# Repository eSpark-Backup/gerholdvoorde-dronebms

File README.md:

# Gerhold Voorde - Drone BMS Circuit Design

## Project Requirements
[Requirements Document](https://docs.google.com/document/d/1HwCwU0NZK4SfBbceRvGtYb6am0WZ7dugDeT3MsA2zgc/edit?usp=sharing)  
[Datasheet](https://www.analog.com/media/en/technical-documentation/data-sheets/MAX17201-MAX17215.pdf)  
[PCB Design Document](https://www.analog.com/media/en/technical-documentation/user-guides/max1720xmax1721x-system-side-implementation-guide.pdf)

### Important Points
* PCB should be designed considering maximum of 20A of discharge current from the battery.
* See possiblity and create overlay for battery so that it makes it convenient for placement in future.

### Reference component URLs
1. https://nl.farnell.com/multicomp/mcwr06x1500ftl/res-150r-1-0-1w-0603-thick-film/dp/2446572
2. https://nl.farnell.com/tdk/c1608x7r1v474k080ae/cap-0-47uf-35v-mlcc-0603/dp/3489827
3. https://nl.farnell.com/multicomp-pro/mcsr06x103-jtl/res-10k-5-0-1w-0603-thick-film/dp/2074170
4. https://nl.farnell.com/multicomp/mc0603b104j160ct/cap-0-1-f-16v-5-x7r-0603-reel/dp/2310627

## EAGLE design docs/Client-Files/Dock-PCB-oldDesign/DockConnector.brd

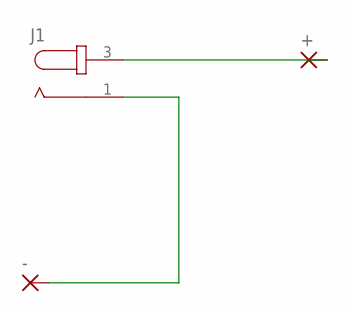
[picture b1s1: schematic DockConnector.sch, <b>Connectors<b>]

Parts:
+: WIREPAD_2,54/1,1
-: WIREPAD_2,54/1,1
J1: CON-JACK_JACK-PLUG0; CON-JACK_SPC4077

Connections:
unnamed: +.1, J1.3
unnamed: -.1, J1.1

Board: 2 copper layers, 3 parts (0 on the bottom side), 2 nets, no tracks yet.

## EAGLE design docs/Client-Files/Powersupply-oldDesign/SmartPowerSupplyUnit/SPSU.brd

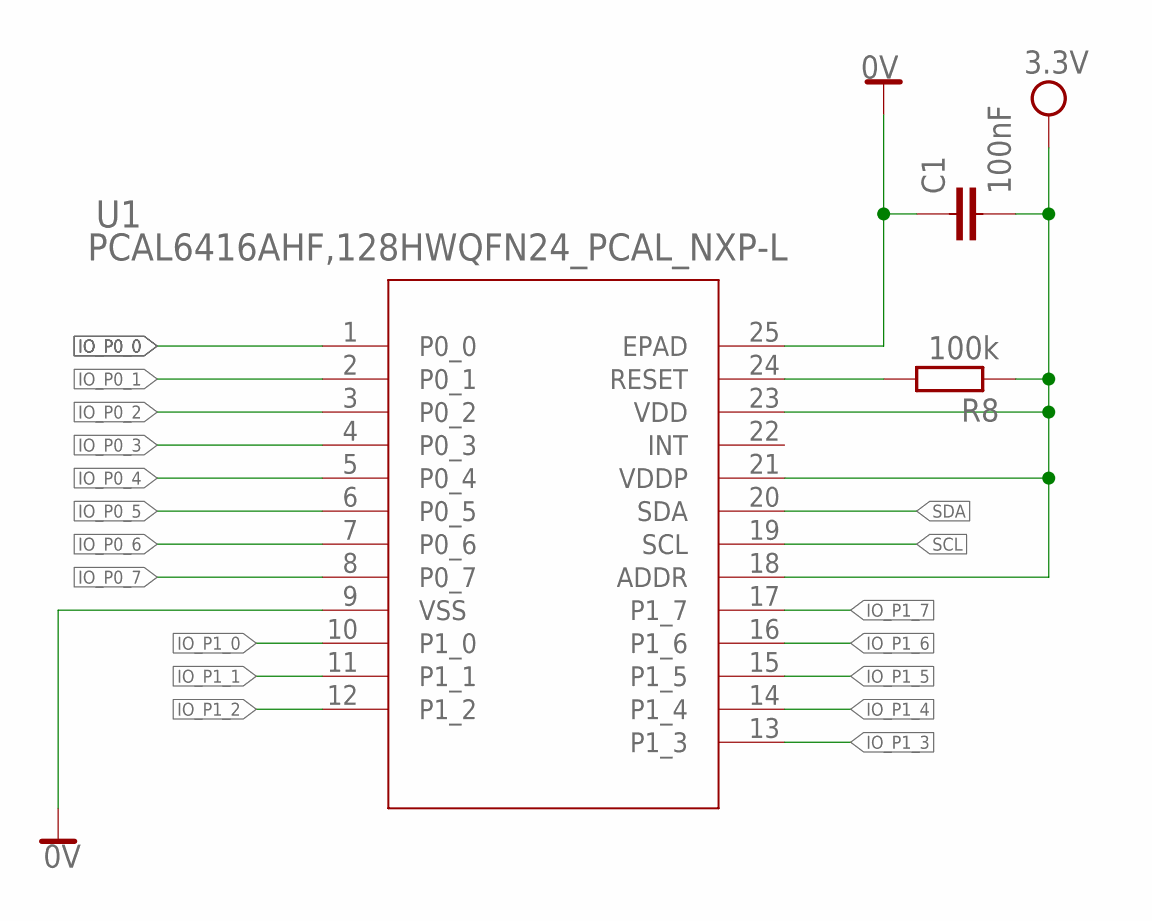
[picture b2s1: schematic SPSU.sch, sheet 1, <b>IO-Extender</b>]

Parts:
C1: 100nF; C0603
R8: 100k; R0603; FARNELL 2447226
U1: PCAL6416AHF,128HWQFN24_PCAL_NXP-L; HWQFN24_PCAL_NXP-L

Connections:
0V: C1.1, U1.9 (VSS), U1.25 (EPAD); also elsewhere on the board
IO_P0_0: U1.1 (P0_0); also elsewhere on the board
IO_P0_1: U1.2 (P0_1); also elsewhere on the board
IO_P0_2: U1.3 (P0_2); also elsewhere on the board
IO_P0_3: U1.4 (P0_3); also elsewhere on the board
IO_P0_4: U1.5 (P0_4); also elsewhere on the board
IO_P0_5: U1.6 (P0_5); also elsewhere on the board
IO_P0_6: U1.7 (P0_6); also elsewhere on the board
IO_P0_7: U1.8 (P0_7)
IO_P1_0: U1.10 (P1_0)
IO_P1_1: U1.11 (P1_1)
IO_P1_2: U1.12 (P1_2); also elsewhere on the board
IO_P1_3: U1.13 (P1_3)
IO_P1_4: U1.14 (P1_4)
IO_P1_5: U1.15 (P1_5)
IO_P1_6: U1.16 (P1_6)
IO_P1_7: U1.17 (P1_7)
unnamed: R8.2, U1.24 (RESET)
SCL: U1.19 (SCL); also elsewhere on the board
SDA: U1.20 (SDA); also elsewhere on the board
VDD: C1.2, R8.1, U1.18 (ADDR), U1.21 (VDDP), U1.23 (VDD); also elsewhere on the board

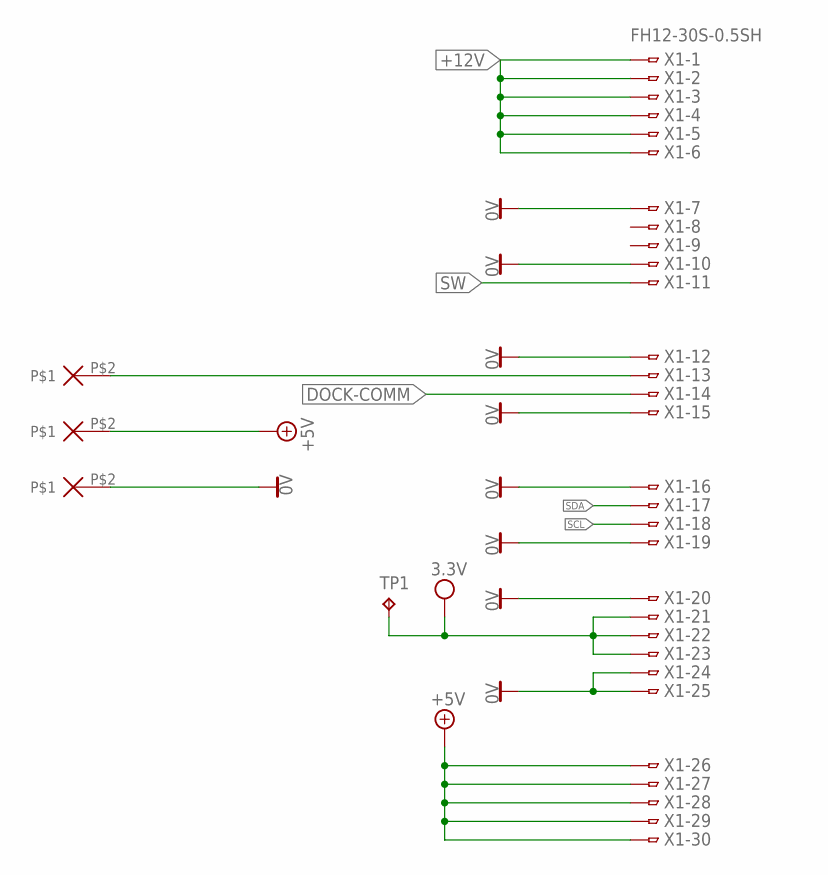
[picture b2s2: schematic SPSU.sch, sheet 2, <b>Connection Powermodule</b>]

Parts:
+: TH-0.75/0.6
-: TH-0.75/0.6
D: TH-0.75/0.6
TP1: TPTP11R; TP11R
X1: FH12-30S-0.5SH

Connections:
0V: -.P$2, X1.7, X1.10, X1.12, X1.15, X1.16, X1.19, X1.20, X1.24, X1.25; also elsewhere on the board
+5V: +.P$2, X1.26, X1.27, X1.28, X1.29, X1.30; also elsewhere on the board
+12V: X1.1, X1.2, X1.3, X1.4, X1.5, X1.6; also elsewhere on the board
DOCK-COMM: X1.14; also elsewhere on the board
unnamed: D.P$2, X1.13
SCL: X1.18; also elsewhere on the board
SDA: X1.17; also elsewhere on the board
SW: X1.11; also elsewhere on the board
VDD: TP1.TP, X1.21, X1.22, X1.23; also elsewhere on the board

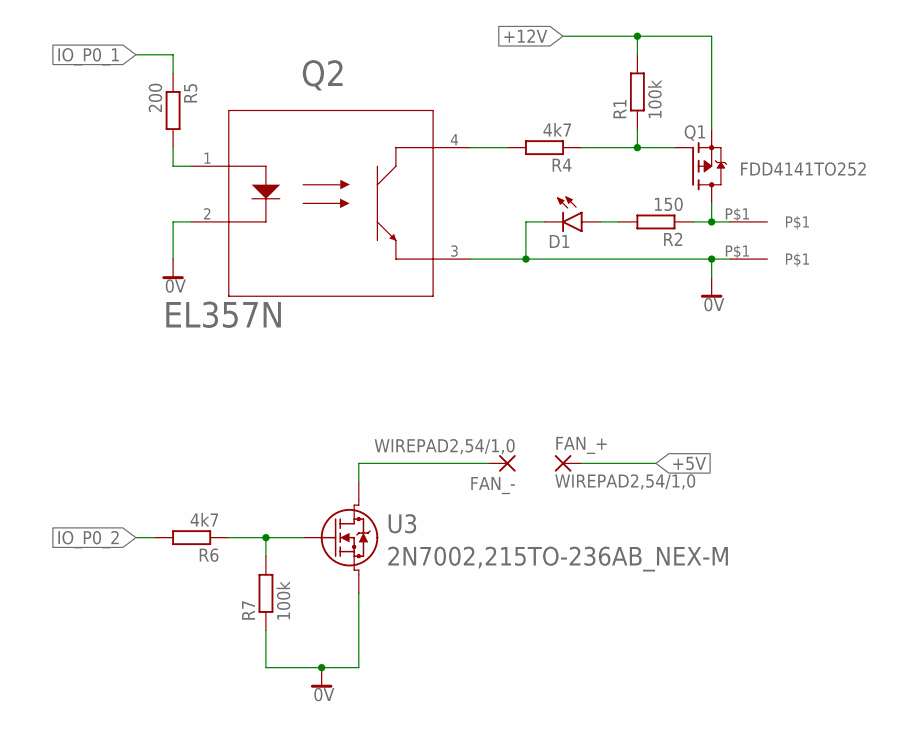
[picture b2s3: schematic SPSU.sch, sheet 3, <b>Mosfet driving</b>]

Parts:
D1: LEDCHIPLED_0805; CHIPLED_0805
ESC+: ESC
ESC-: ESC
FAN_+: WIREPAD2,54/1,0; 2,54/1,0
FAN_-: WIREPAD2,54/1,0; 2,54/1,0
Q1: FDD4141TO252; TO252
Q2: EL357N; EL357N(C)(TA)-VG_EVE-L
R1, R7: 100k; R0603
R2: 150; R0603
R4, R6: 4k7; R0603
R5: 200; R0603
U3: 2N7002,215TO-236AB_NEX-M; TO-236AB_NEX-M

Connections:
0V: D1.C, ESC-.P$1, Q2.2, Q2.3, R7.1, U3.2 (3); also elsewhere on the board
+5V: FAN_+.1; also elsewhere on the board
+12V: Q1.2 (S), R1.2; also elsewhere on the board
ESC_+: ESC+.P$1, Q1.3 (D), R2.1
IO_P0_1: R5.1; also elsewhere on the board
IO_P0_2: R6.2; also elsewhere on the board
unnamed: Q1.1 (G), R1.1, R4.1
unnamed: D1.A, R2.2
unnamed: Q2.4, R4.2
unnamed: Q2.1, R5.2
unnamed: R6.1, R7.2, U3.1
unnamed: FAN_-.1, U3.3 (2)

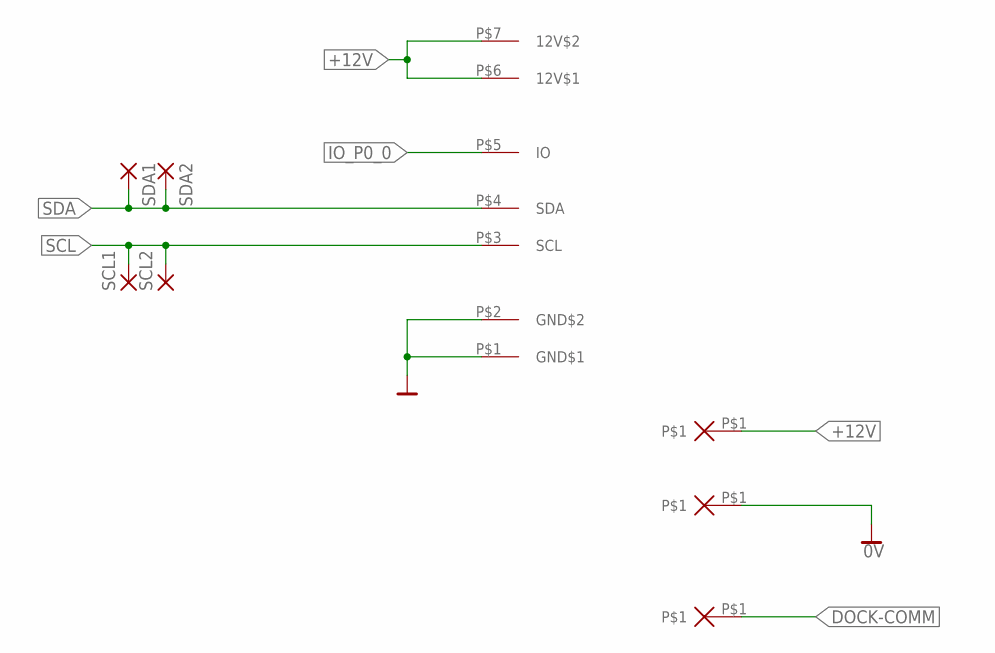
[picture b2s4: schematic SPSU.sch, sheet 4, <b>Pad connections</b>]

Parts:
CHG+: SMT-PAD_SQ6MM
CHG-: SMT-PAD_SQ6MM
SCL1, SCL2: 1,6/0,8
SDA1, SDA2: 1,6/0,8
U$1: BATT_CON_THT
U$2: SMT-PAD_R3MM

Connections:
0V: CHG-.P$1, U$1.P$1 (GND$1), U$1.P$2 (GND$2); also elsewhere on the board
+12V: CHG+.P$1, U$1.P$6 (12V$1), U$1.P$7 (12V$2); also elsewhere on the board
DOCK-COMM: U$2.P$1; also elsewhere on the board
IO_P0_0: U$1.P$5 (IO); also elsewhere on the board
SCL: SCL1.1, SCL2.1, U$1.P$3 (SCL); also elsewhere on the board
SDA: SDA1.1, SDA2.1, U$1.P$4 (SDA); also elsewhere on the board

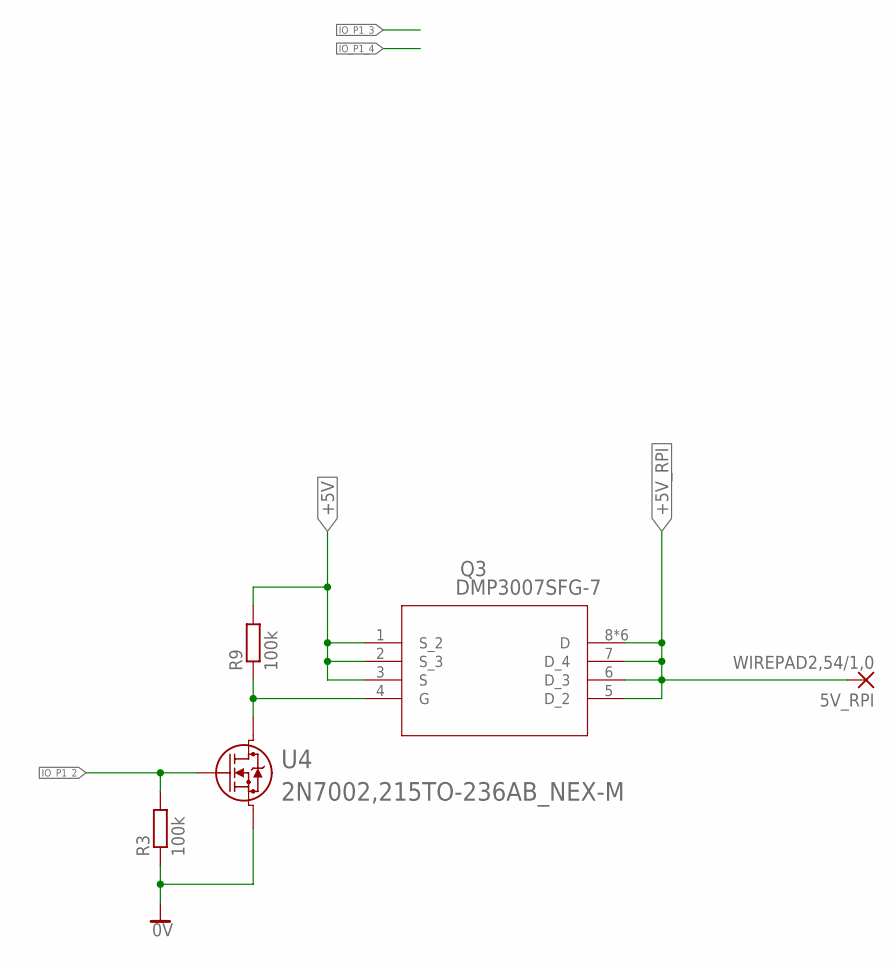
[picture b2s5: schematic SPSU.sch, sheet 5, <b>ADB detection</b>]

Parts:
5V_RPI: WIREPAD2,54/1,0; 2,54/1,0
Q3: DMP3007SFG-7; POWERDI3333-8_3P3X3P3_DIO
R3, R9: 100k; R0603
U4: 2N7002,215TO-236AB_NEX-M; TO-236AB_NEX-M

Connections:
0V: R3.1, U4.2 (3); also elsewhere on the board
+5V: Q3.1 (S_2), Q3.2 (S_3), Q3.3 (S), R9.2; also elsewhere on the board
+5V_RPI: 5V_RPI.1, Q3.5 (D_2), Q3.6 (D_3), Q3.7 (D_4), Q3.8 (D), Q3.9 (D), Q3.10 (D), Q3.11 (D), Q3.12 (D), Q3.13 (D)
IO_P1_2: R3.2, U4.1; also elsewhere on the board
unnamed: Q3.4 (G), R9.1, U4.3 (2)

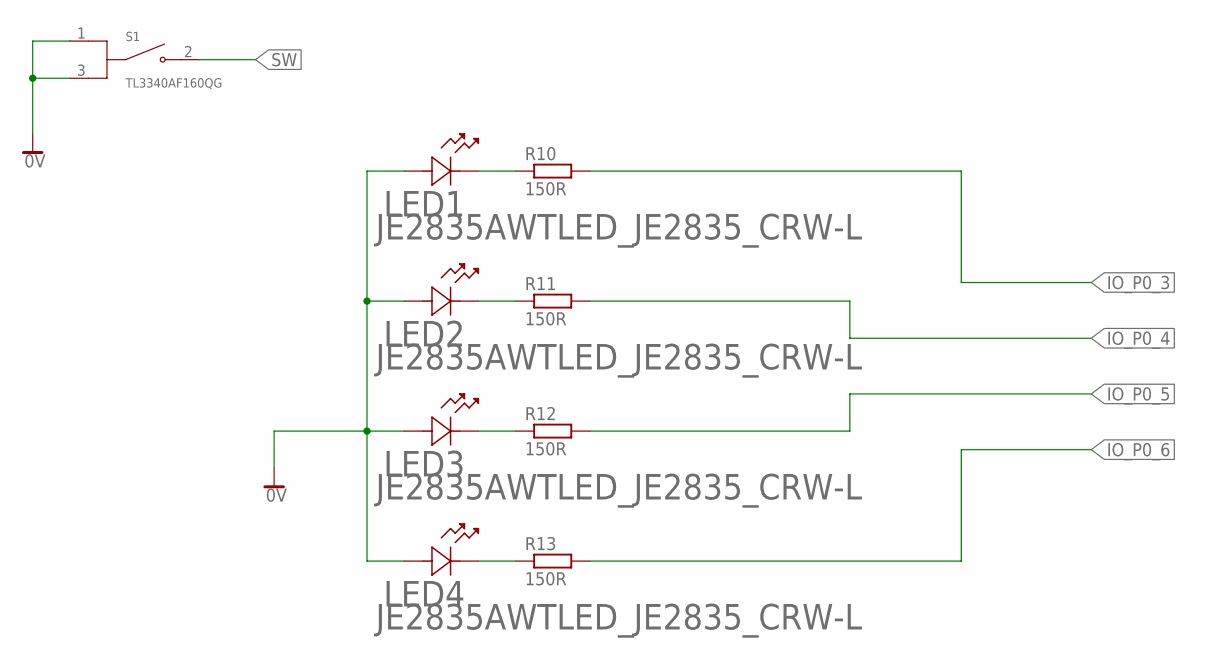
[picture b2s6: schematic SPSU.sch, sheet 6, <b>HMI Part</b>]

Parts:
LED1, LED2, LED3, LED4: JE2835AWTLED_JE2835_CRW-L; LED_JE2835_CRW-L
R10, R11, R12, R13: 150R; R0603
S1: TL3340AF160QG; SW_TL3340AF160QG

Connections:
0V: LED1.1 (2), LED2.1 (2), LED3.1 (2), LED4.1 (2), S1.1 (COM_1), S1.3 (COM_2); also elsewhere on the board
IO_P0_3: R10.2; also elsewhere on the board
IO_P0_4: R11.2; also elsewhere on the board
IO_P0_5: R12.2; also elsewhere on the board
IO_P0_6: R13.2; also elsewhere on the board
unnamed: LED1.2 (1), R10.1
unnamed: LED2.2 (1), R11.1
unnamed: LED3.2 (1), R12.1
unnamed: LED4.2 (1), R13.1
SW: S1.2 (NO); also elsewhere on the board

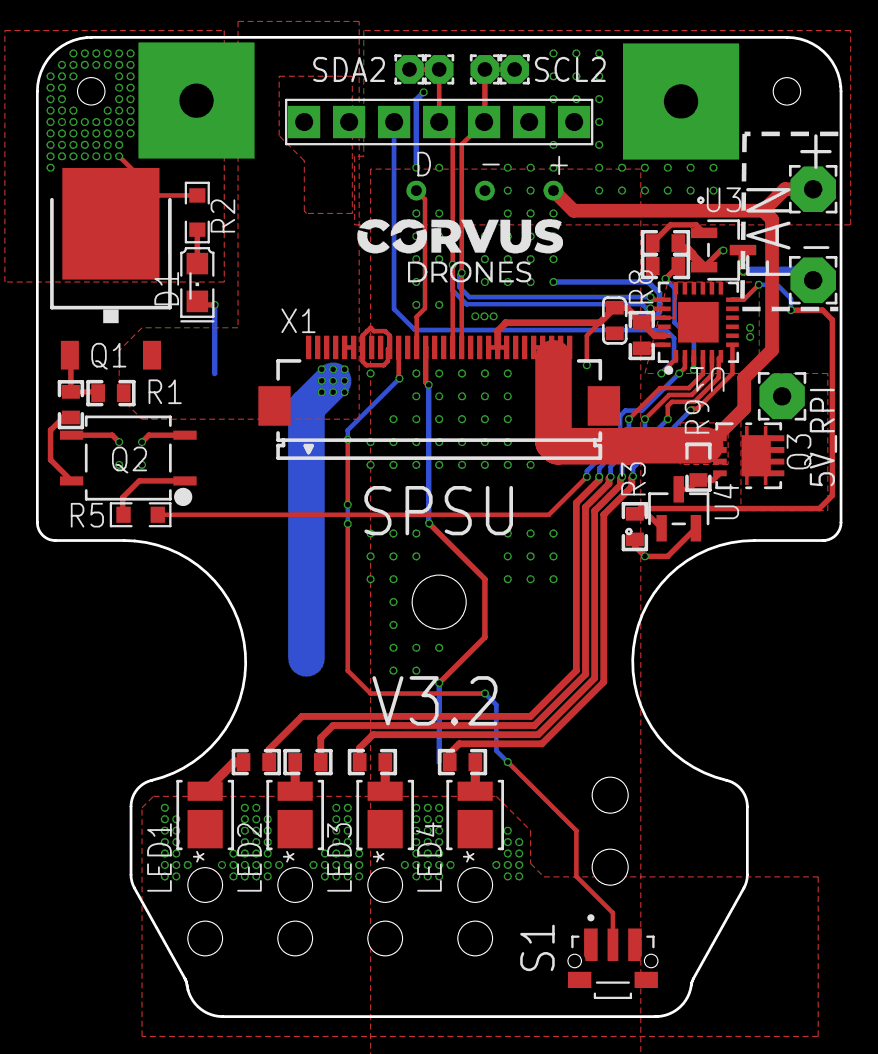
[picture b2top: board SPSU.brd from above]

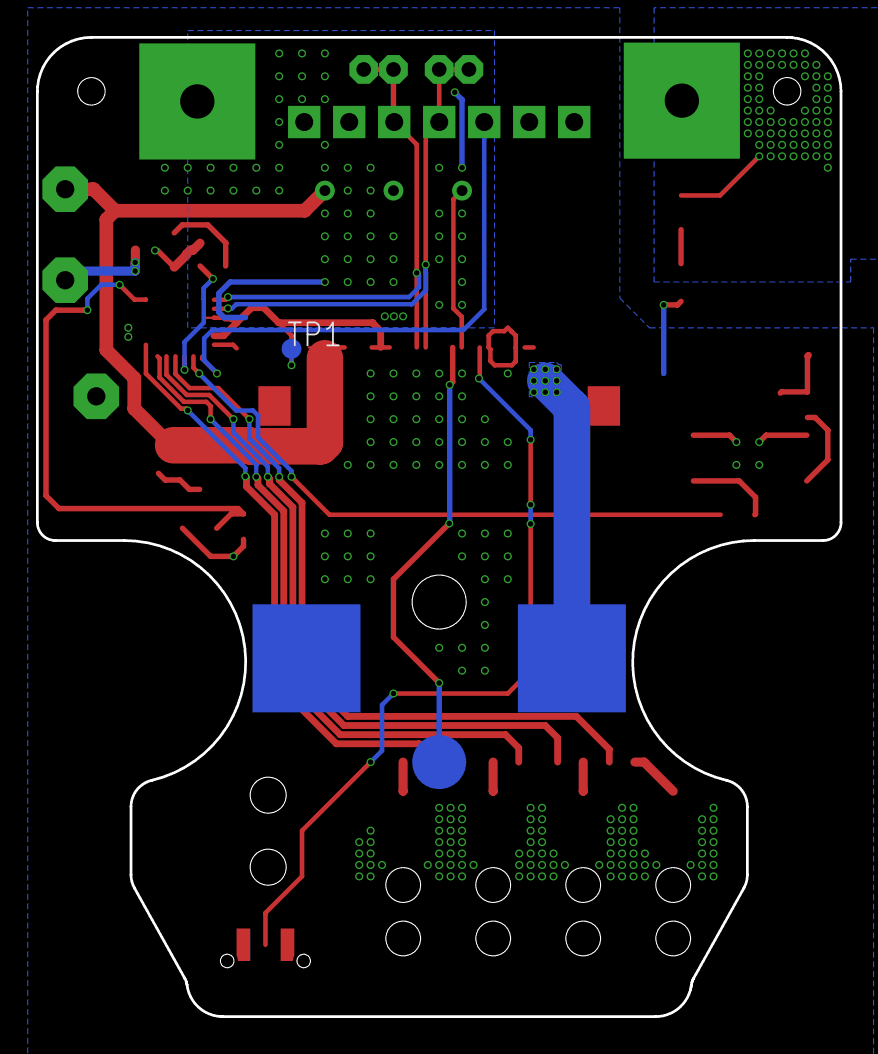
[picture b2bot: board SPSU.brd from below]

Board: 2 copper layers, 44.6 x 54.4 mm, 44 parts (4 on the bottom side), 31 nets.

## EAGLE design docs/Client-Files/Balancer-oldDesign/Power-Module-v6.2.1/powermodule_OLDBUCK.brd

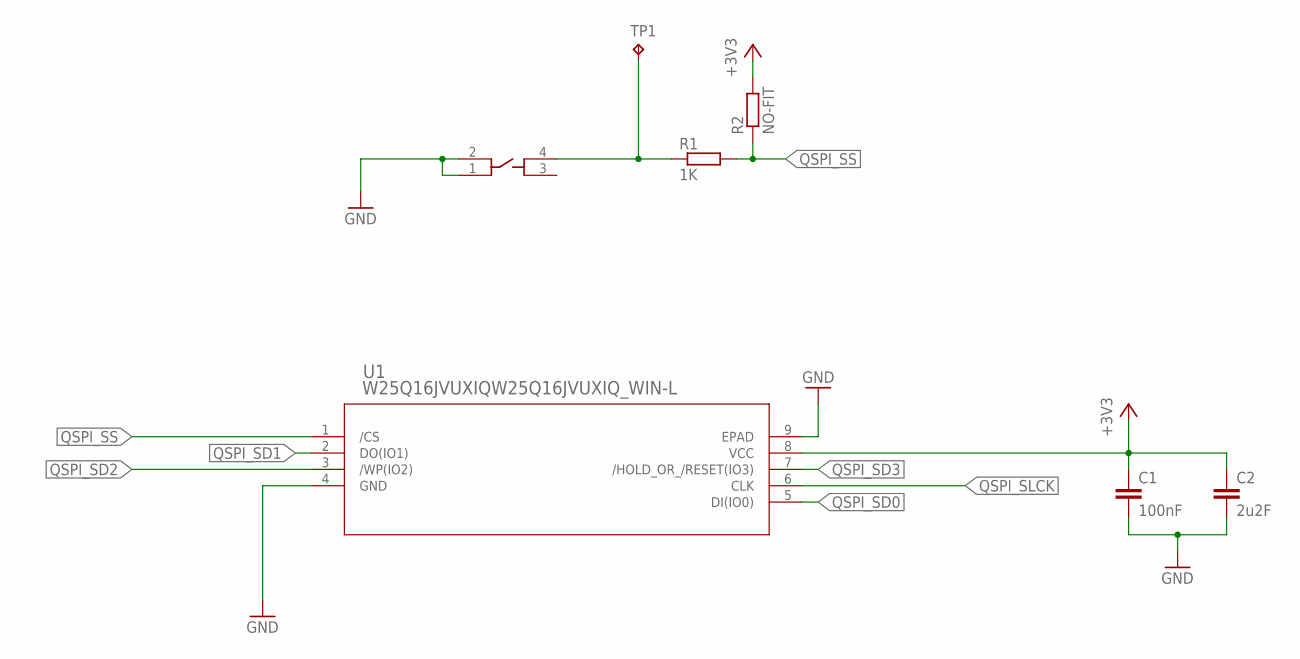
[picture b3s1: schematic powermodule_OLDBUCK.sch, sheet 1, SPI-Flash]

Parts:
C1: 100nF; C0603
C2: 2u2F; C0603
R1: 1K; R0603
R2: NO-FIT; R0603
TP1: TPTP15R; TP15R
U1: W25Q16JVUXIQW25Q16JVUXIQ_WIN-L; W25Q16JVUXIQ_WIN-L
U$7: BOOTSEL; EVQ-P7J01P

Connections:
+3V3: C1.1, C2.1, R2.2, U1.8 (VCC); also elsewhere on the board
GND: C1.2, C2.2, U1.4 (GND), U1.9 (EPAD), U$7.1, U$7.2; also elsewhere on the board
unnamed: R1.1, TP1.TP, U$7.4
QSPI_SD0: U1.5 (DI(IO0)); also elsewhere on the board
QSPI_SD1: U1.2 (DO(IO1)); also elsewhere on the board
QSPI_SD2: U1.3 (/WP(IO2)); also elsewhere on the board
QSPI_SD3: U1.7 (/HOLD_OR_/RESET(IO3)); also elsewhere on the board
QSPI_SLCK: U1.6 (CLK); also elsewhere on the board
QSPI_SS: R1.2, R2.1, U1.1 (/CS); also elsewhere on the board

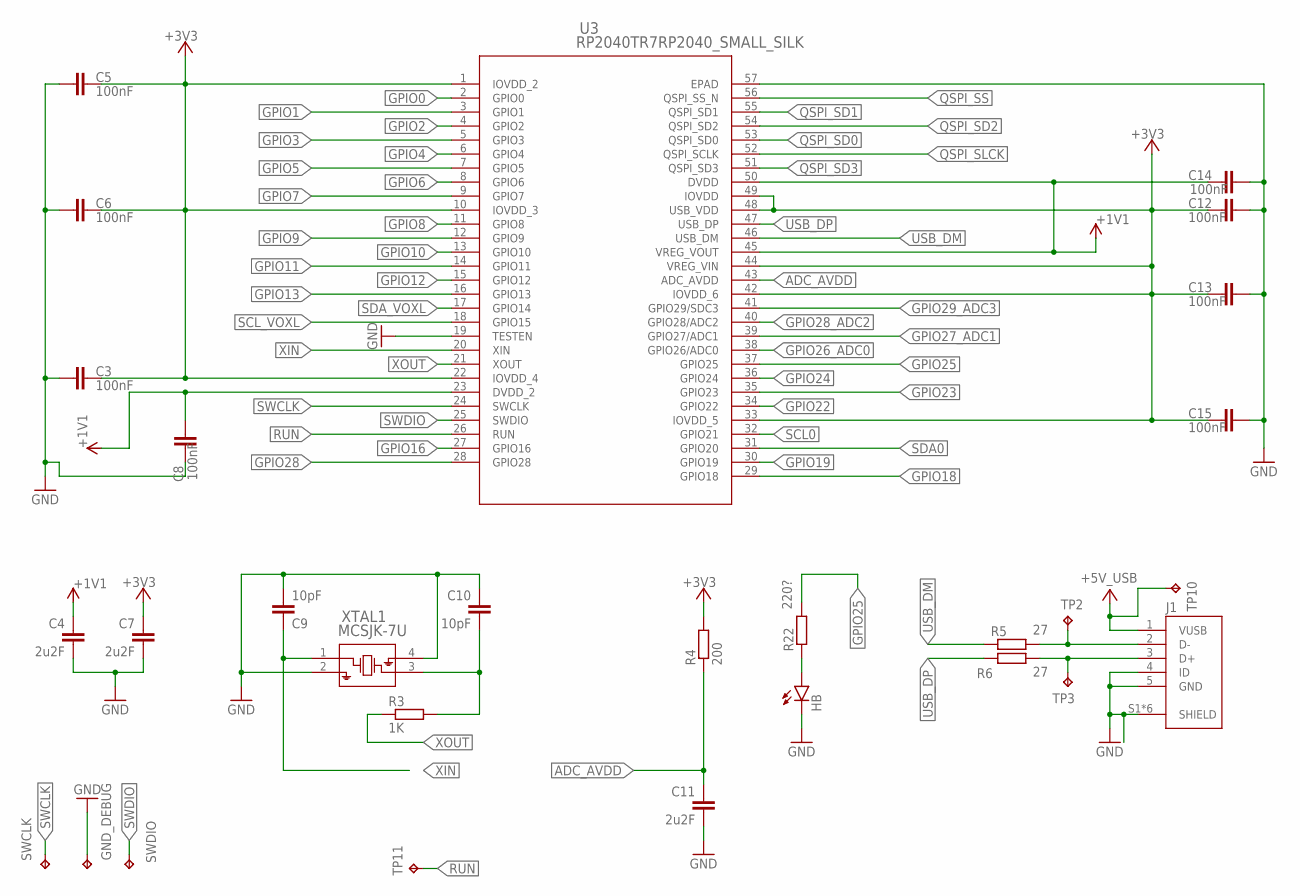
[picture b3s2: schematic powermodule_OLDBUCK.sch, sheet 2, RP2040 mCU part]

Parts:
C3, C5, C6, C8, C12, C13, C14, C15: 100nF; C0603
C4, C7, C11: 2u2F; C0603
C9, C10: 10pF; C0603
GND_DEBUG: TPTP15R; TP15R
HB: LEDCHIPLED_0805; CHIPLED_0805
J1: 10118193-0001LF; FCI_10118193-0001LF
R3: 1K; R0603
R4: 200; R0603
R5, R6: 27; R0603
R22: 220?; R0603
SWCLK: TPTP15R; TP15R
SWDIO: TPTP15R; TP15R
TP2, TP3, TP10, TP11: TPTP15R; TP15R
U3: RP2040TR7RP2040_SMALL_SILK; RP2040TR7_RPI-L_CUSTM
XTAL1: MCSJK-7U; SMD3225_3.2X2.5X0.7_MTC-L

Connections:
+1V1: C4.2, C8.1, C14.2, U3.23 (DVDD_2), U3.45 (VREG_VOUT), U3.50 (DVDD)
+3V3: C3.2, C5.1, C6.1, C7.2, C12.1, C13.1, C15.2, R4.2, U3.1 (IOVDD_2), U3.10 (IOVDD_3), U3.22 (IOVDD_4), U3.33 (IOVDD_5), U3.42 (IOVDD_6), U3.44 (VREG_VIN), U3.48 (USB_VDD), U3.49 (IOVDD); also elsewhere on the board
+5V_USB: J1.1 (VUSB), TP10.TP; also elsewhere on the board
ADC_AVDD: C11.2, R4.1, U3.43 (ADC_AVDD)
GND: C3.1, C4.1, C5.2, C6.2, C7.1, C8.2, C9.1, C10.2, C11.1, C12.2, C13.2, C14.1, C15.1, GND_DEBUG.TP, HB.C, J1.4 (ID), J1.5 (GND), J1.S1 (SHIELD), J1.S2 (SHIELD), J1.S3 (SHIELD), J1.S4 (SHIELD), J1.S5 (SHIELD), J1.S6 (SHIELD), U3.19 (TESTEN), U3.57 (EPAD), XTAL1.2, XTAL1.4; also elsewhere on the board
GPIO0: U3.2 (GPIO0)
GPIO1: U3.3 (GPIO1)
GPIO2: U3.4 (GPIO2)
GPIO3: U3.5 (GPIO3)
GPIO4: U3.6 (GPIO4)
GPIO5: U3.7 (GPIO5)
GPIO6: U3.8 (GPIO6)
GPIO7: U3.9 (GPIO7)
GPIO8: U3.11 (GPIO8)
GPIO9: U3.12 (GPIO9)
GPIO10: U3.13 (GPIO10)
GPIO11: U3.14 (GPIO11)
GPIO12: U3.15 (GPIO12)
GPIO13: U3.16 (GPIO13); also elsewhere on the board
GPIO16: U3.27 (GPIO16)
GPIO18: U3.29 (GPIO18); also elsewhere on the board
GPIO19: U3.30 (GPIO19); also elsewhere on the board
GPIO22: U3.34 (GPIO22)
GPIO23: U3.35 (GPIO23); also elsewhere on the board
GPIO24: U3.36 (GPIO24); also elsewhere on the board
GPIO25: R22.2, U3.37 (GPIO25)
GPIO26_ADC0: U3.38 (GPIO26/ADC0)
GPIO27_ADC1: U3.39 (GPIO27/ADC1)
GPIO28: U3.28 (GPIO28)
GPIO28_ADC2: U3.40 (GPIO28/ADC2)
GPIO29_ADC3: U3.41 (GPIO29/SDC3)
unnamed: C10.1, R3.2, XTAL1.3
unnamed: HB.A, R22.1
QSPI_SD0: U3.53 (QSPI_SD0); also elsewhere on the board
QSPI_SD1: U3.55 (QSPI_SD1); also elsewhere on the board
QSPI_SD2: U3.54 (QSPI_SD2); also elsewhere on the board
QSPI_SD3: U3.51 (QSPI_SD3); also elsewhere on the board
QSPI_SLCK: U3.52 (QSPI_SCLK); also elsewhere on the board
QSPI_SS: U3.56 (QSPI_SS_N); also elsewhere on the board
RUN: TP11.TP, U3.26 (RUN)
SCL0: U3.32 (GPIO21); also elsewhere on the board
SCL_VOXL: U3.18 (GPIO15); also elsewhere on the board
SDA0: U3.31 (GPIO20); also elsewhere on the board
SDA_VOXL: U3.17 (GPIO14); also elsewhere on the board
SWCLK: SWCLK.TP, U3.24 (SWCLK)
SWDIO: SWDIO.TP, U3.25 (SWDIO)
USBM_DM: J1.2 (D-), R5.2, TP2.TP; also elsewhere on the board
USBM_DP: J1.3 (D+), R6.2, TP3.TP; also elsewhere on the board
USB_DM: R5.1, U3.46 (USB_DM)
USB_DP: R6.1, U3.47 (USB_DP)
XIN: C9.2, U3.20 (XIN), XTAL1.1
XOUT: R3.1, U3.21 (XOUT)

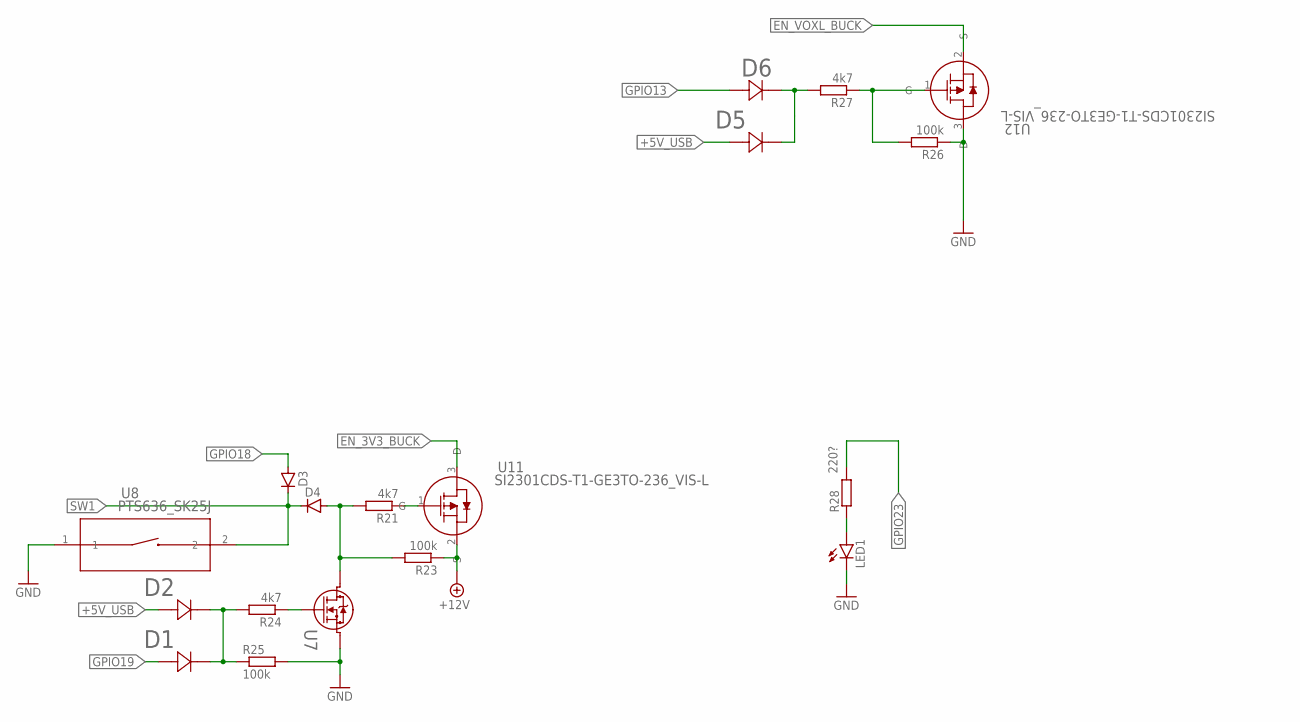
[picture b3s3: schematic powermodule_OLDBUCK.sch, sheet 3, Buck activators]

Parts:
D1, D2, D5, D6: 1N4148WS-7-FSOD323_DIO-L; SOD323_DIO-L
D3, D4: CGRM4002-G; SOD-123_MINI-SMA
LED1: LEDCHIPLED_0805; CHIPLED_0805
R21, R24, R27: 4k7; R0603
R23, R25, R26: 100k; R0603
R28: 220?; R0603
U7: 2N7002,215TO-236AB_NEX-L; TO-236AB_NEX-L
U8: PTS636_SK25J; SW_PTS636_SK25J_SMTR_LFS_CNK-M
U11, U12: SI2301CDS-T1-GE3TO-236_VIS-L; TO-236_VIS-L

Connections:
+5V_USB: D2.2, D5.2; also elsewhere on the board
+12V: R23.1, U11.2 (S); also elsewhere on the board
EN_3V3_BUCK: U11.3 (D); also elsewhere on the board
EN_VOXL_BUCK: U12.2 (S); also elsewhere on the board
GND: LED1.C, R25.2, R26.1, U7.2 (3), U8.1, U12.3 (D); also elsewhere on the board
GPIO13: D6.2; also elsewhere on the board
GPIO18: D3.A; also elsewhere on the board
GPIO19: D1.2; also elsewhere on the board
GPIO23: R28.2; also elsewhere on the board
unnamed: R21.1, U11.1 (G)
unnamed: D5.1, D6.1, R27.2
unnamed: D4.A, R21.2, R23.2, U7.3 (2)
unnamed: R26.2, R27.1, U12.1 (G)
unnamed: R24.1, U7.1
unnamed: LED1.A, R28.1
unnamed: D1.1, D2.1, R24.2, R25.1
SW1: D3.C, D4.C, U8.2; also elsewhere on the board

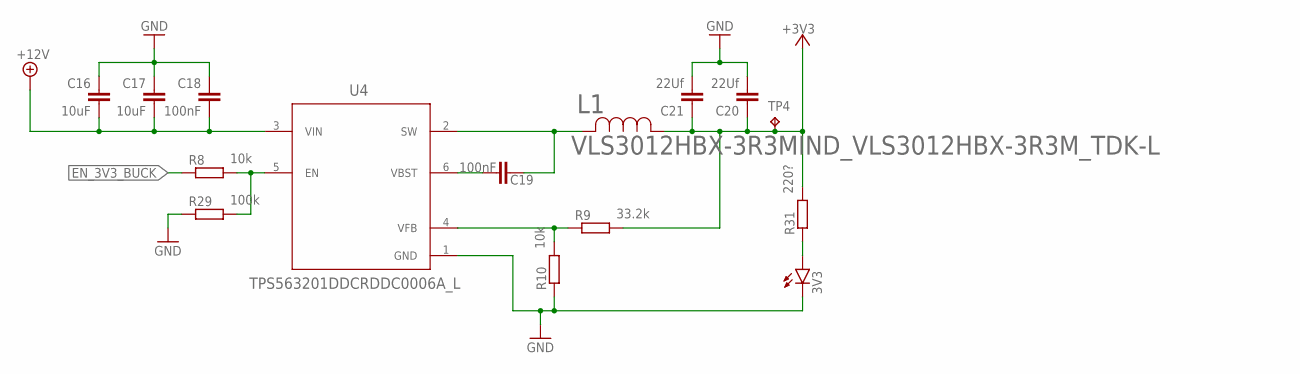
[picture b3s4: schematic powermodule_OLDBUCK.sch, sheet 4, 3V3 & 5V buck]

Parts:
3V3: LEDCHIPLED_0805; CHIPLED_0805
C16, C17: 10uF; C0603
C18, C19: 100nF; C0603
C20, C21: 22Uf; C1206
L1: VLS3012HBX-3R3MIND_VLS3012HBX-3R3M_TDK-L; IND_VLS3012HBX-3R3M_TDK-L
R8, R10: 10k; R0603
R9: 33.2k; R0603
R29: 100k; R0603
R31: 220?; R0603
TP4: TPTP15R; TP15R
U4: TPS563201DDCRDDC0006A_L; DDC0006A_L

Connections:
+3V3: C20.1, C21.1, L1.1, R9.2, R31.2, TP4.TP; also elsewhere on the board
+12V: C16.1, C17.1, C18.1, U4.3 (VIN); also elsewhere on the board
EN_3V3_BUCK: R8.1; also elsewhere on the board
GND: 3V3.C, C16.2, C17.2, C18.2, C20.2, C21.2, R10.1, R29.1, U4.1 (GND); also elsewhere on the board
unnamed: R8.2, R29.2, U4.5 (EN)
unnamed: R9.1, R10.2, U4.4 (VFB)
unnamed: C19.1, U4.6 (VBST)
unnamed: C19.2, L1.2, U4.2 (SW)
unnamed: 3V3.A, R31.1

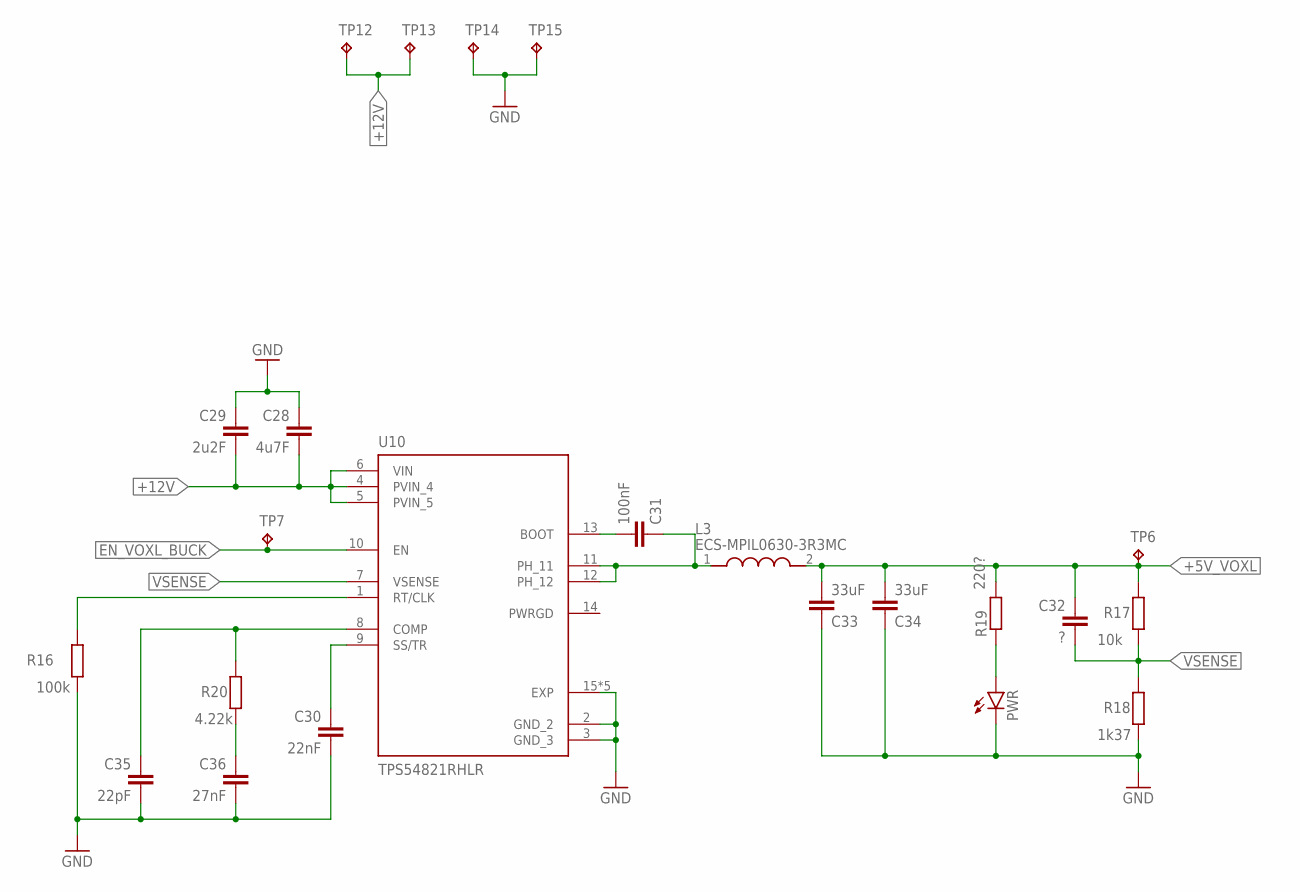
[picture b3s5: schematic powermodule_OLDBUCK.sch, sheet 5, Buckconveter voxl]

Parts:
C28: 4u7F; C0805
C29: 2u2F; C0805
C30: 22nF; C0603
C31: 100nF; C0603
C32: ?; C0603
C33, C34: 33uF; C1206
C35: 22pF; C0603
C36: 27nF; C0603
L3: ECS-MPIL0630-3R3MC; IND_ECS-MPIL0630-3R3MC
PWR: LEDCHIPLED_0805; CHIPLED_0805
R16: 100k; R0603
R17: 10k; R0603
R18: 1k37; R0603
R19: 220?; R0603
R20: 4.22k; R0603
TP6, TP7, TP12, TP13, TP14, TP15: TPTP15R; TP15R
U10: TPS54821RHLR; IC_TPS54821RHLR

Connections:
+5V_VOXL: C32.2, C33.1, C34.1, L3.2, R17.2, R19.2, TP6.TP; also elsewhere on the board
+12V: C28.1, C29.1, TP12.TP, TP13.TP, U10.4 (PVIN_4), U10.5 (PVIN_5), U10.6 (VIN); also elsewhere on the board
EN_VOXL_BUCK: TP7.TP, U10.10 (EN); also elsewhere on the board
GND: C28.2, C29.2, C30.1, C33.2, C34.2, C35.1, C36.1, PWR.C, R16.1, R18.1, TP14.TP, TP15.TP, U10.2 (GND_2), U10.3 (GND_3), U10.15 (EXP), U10.16 (EXP), U10.17 (EXP), U10.18 (EXP), U10.19 (EXP); also elsewhere on the board
unnamed: R16.2, U10.1 (RT/CLK)
unnamed: C31.2, L3.1, U10.11 (PH_11), U10.12 (PH_12)
unnamed: C30.2, U10.9 (SS/TR)
unnamed: C31.1, U10.13 (BOOT)
unnamed: PWR.A, R19.1
unnamed: C35.2, R20.2, U10.8 (COMP)
unnamed: C36.2, R20.1
VSENSE: C32.1, R17.1, R18.2, U10.7 (VSENSE)

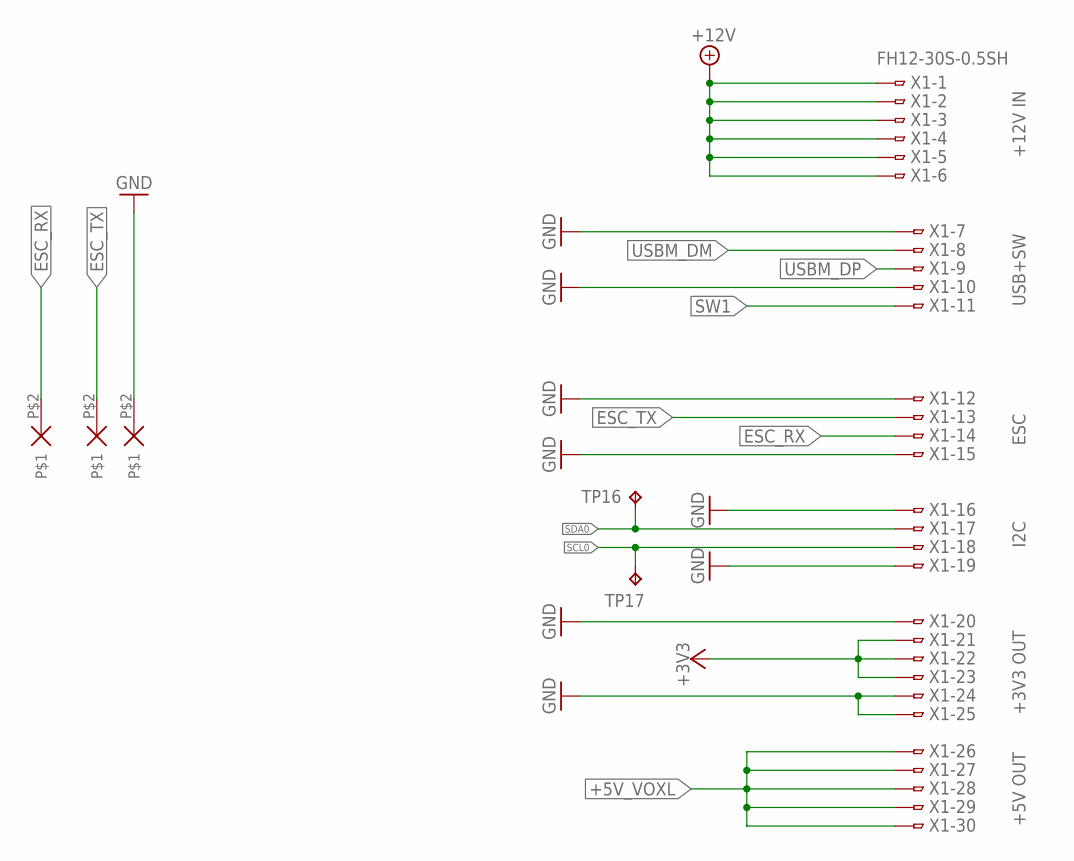
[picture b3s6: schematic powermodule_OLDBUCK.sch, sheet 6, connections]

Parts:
EGND: TH-0.75/0.6
RX: TH-0.75/0.6
TP16, TP17: TPTP15R; TP15R
TX: TH-0.75/0.6
X1: FH12-30S-0.5SH

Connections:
+3V3: X1.21, X1.22, X1.23; also elsewhere on the board
+5V_VOXL: X1.26, X1.27, X1.28, X1.29, X1.30; also elsewhere on the board
+12V: X1.1, X1.2, X1.3, X1.4, X1.5, X1.6; also elsewhere on the board
ESC_RX: RX.P$2, X1.14
ESC_TX: TX.P$2, X1.13
GND: EGND.P$2, X1.7, X1.10, X1.12, X1.15, X1.16, X1.19, X1.20, X1.24, X1.25; also elsewhere on the board
SCL0: TP17.TP, X1.18; also elsewhere on the board
SDA0: TP16.TP, X1.17; also elsewhere on the board
SW1: X1.11; also elsewhere on the board
USBM_DM: X1.8; also elsewhere on the board
USBM_DP: X1.9; also elsewhere on the board

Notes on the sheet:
+5V OUT
+3V3 OUT
I2C
ESC
USB+SW
+12V IN

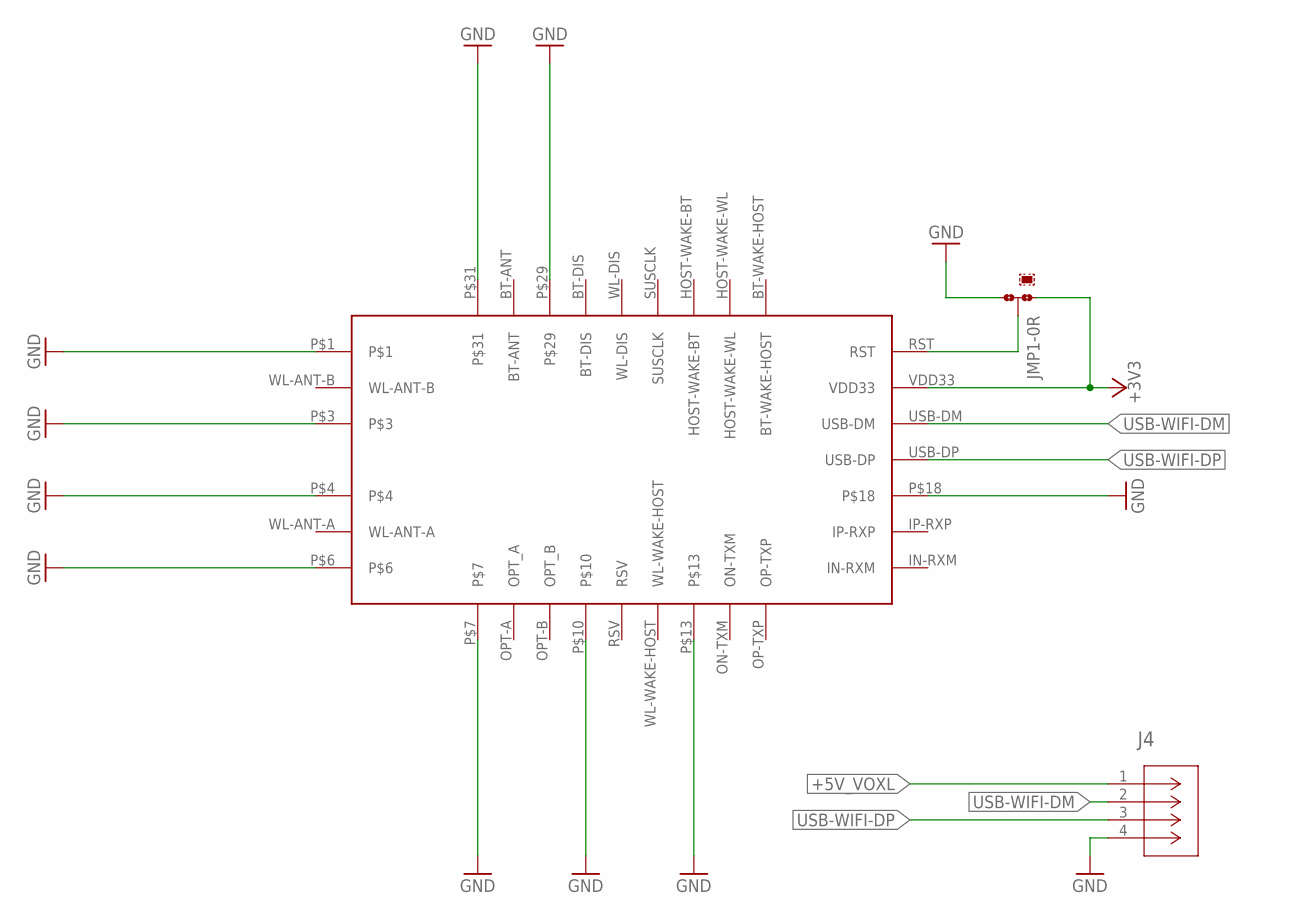
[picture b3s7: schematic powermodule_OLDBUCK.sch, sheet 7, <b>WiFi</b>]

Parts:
J4: USB1125-GF-B; CONN_USB1125-GF-B_GCT
JMP1: 0R-JUMPA; A0R-JMP
U$5: WIFI-RTL8822BU

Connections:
+3V3: JMP1.1, U$5.VDD33; also elsewhere on the board
+5V_VOXL: J4.1; also elsewhere on the board
GND: J4.4, JMP1.3, U$5.P$1, U$5.P$3, U$5.P$4, U$5.P$6, U$5.P$7, U$5.P$10, U$5.P$13, U$5.P$18, U$5.P$29, U$5.P$31; also elsewhere on the board
unnamed: JMP1.2, U$5.RST
USB-WIFI-DM: J4.2, U$5.USB-DM; also elsewhere on the board
USB-WIFI-DP: J4.3, U$5.USB-DP; also elsewhere on the board

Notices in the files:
parts and their libraries:
COPYRIGHT: Copyright (C) 2022 Ultra Librarian. All rights reserved.
COPYRIGHT: Copyright (C) 2023 Ultra Librarian. All rights reserved.
